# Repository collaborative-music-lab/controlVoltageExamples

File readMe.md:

# controlVoltageExamples

Files for creating Eurorack modules based on the controlVoltage repository: https://github.com/ianhattwick/controlVoltage

### Standard examples
Three examples so far:
* 8-step trigger sequencer
* Sloopy: dual slope generator
* dual LFO (missing?)
* Voxelist: Dual input quantizer

## Also examples of using USB Midi devices to generated sequences

### Requires
Note: all libraries available through library manager
EXCEPT: Control Voltage needs most recent version from Github

1. Arduino USB Host shield 
	* https://github.com/felis/USB_Host_Shield_2.0
2. Hitachi style 2x16 LCD display with I2C backpack
	* https://github.com/marcoschwartz/LiquidCrystal_I2C.git
3. Control Voltage library
	* https://github.com/ianhattwick/controlVoltage
4. Standard EEPROM library

### examples
1. Harpy - Launchkey controlling NiftyCase with melodic voice
2. Leonard - Launchpad 2 controlling NiftyCase with rhythmic voice
3. Tyrone - nanokontrol2 controlling Roland T-8

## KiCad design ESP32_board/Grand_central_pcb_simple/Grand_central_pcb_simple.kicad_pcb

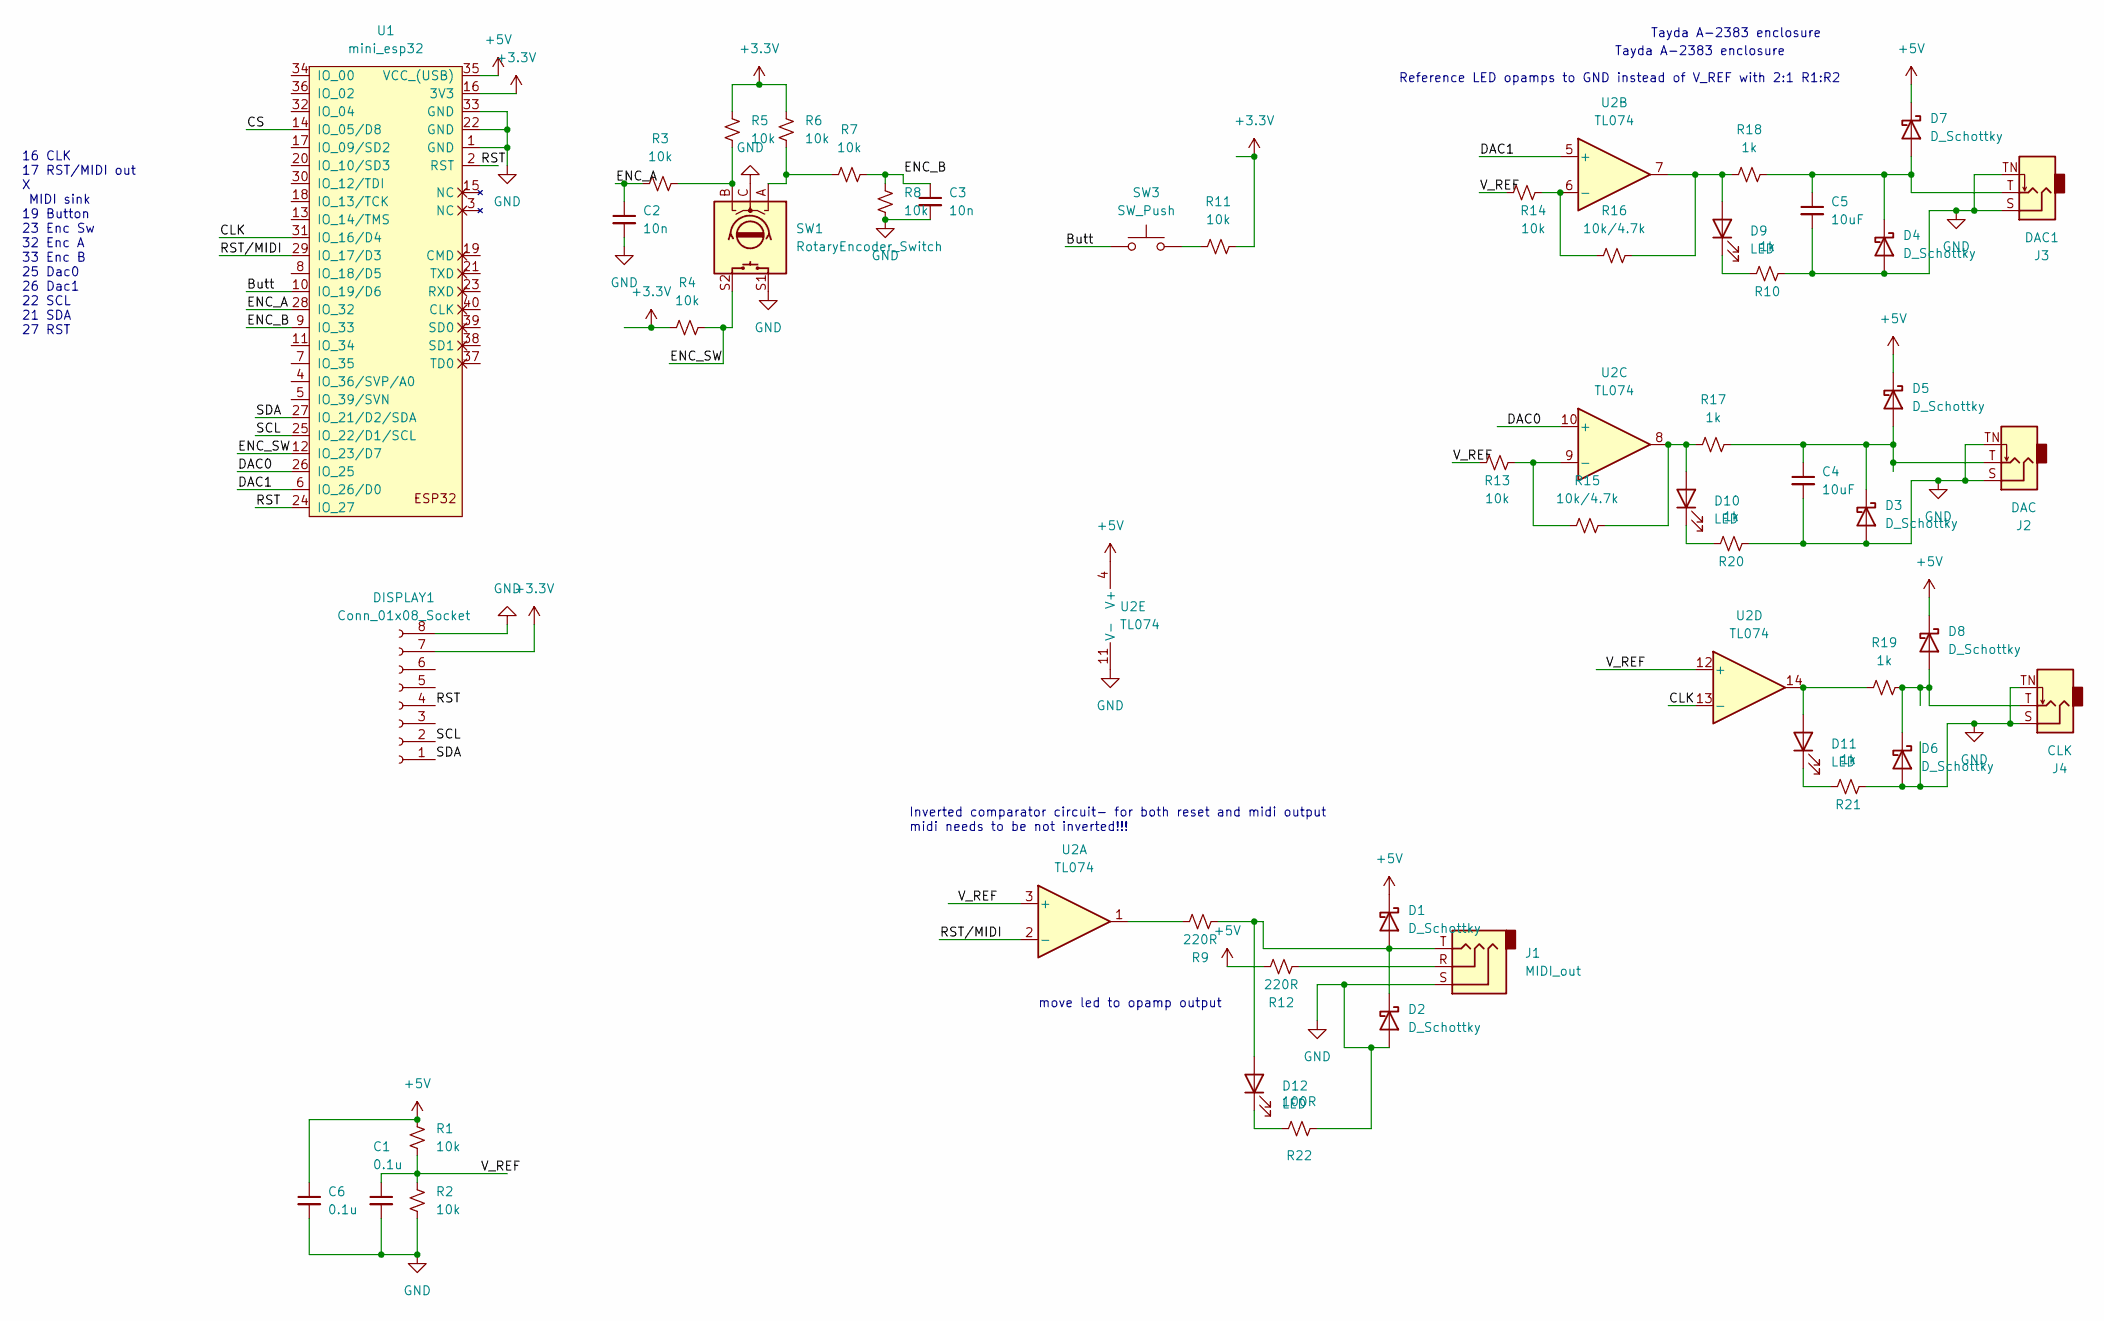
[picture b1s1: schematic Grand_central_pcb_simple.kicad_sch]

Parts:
C1, C6: 0.1u; C_0805_2012Metric_Pad1.18x1.45mm_HandSolder
C2, C3: 10n; C_0805_2012Metric_Pad1.18x1.45mm_HandSolder
C4, C5: 10uF; C_0805_2012Metric_Pad1.18x1.45mm_HandSolder
D1, D2, D3, D4, D5, D6, D7, D8: D_Schottky; D_SOD-123
D9, D10, D11, D12: LED; LED_D3.0mm
DISPLAY1: Conn_01x08_Socket; Adafruit_SSD1306
J1: MIDI_out; Jack_3.5mm_QingPu_WQP-PJ398SM_Vertical_CircularHoles_1
J2: DAC; Jack_3.5mm_QingPu_WQP-PJ398SM_Vertical_CircularHoles
J3: DAC1; Jack_3.5mm_QingPu_WQP-PJ398SM_Vertical_CircularHoles
J4: CLK; Jack_3.5mm_QingPu_WQP-PJ398SM_Vertical_CircularHoles
R1, R2, R3, R4, R5, R6, R7, R8, R11, R13, R14: 10k; R_0805_2012Metric_Pad1.20x1.40mm_HandSolder
R9, R12: 220R; R_0805_2012Metric_Pad1.20x1.40mm_HandSolder
R10, R17, R18, R19, R20, R21: 1k; R_0805_2012Metric_Pad1.20x1.40mm_HandSolder
R15, R16: 10k/4.7k; R_0805_2012Metric_Pad1.20x1.40mm_HandSolder
R22: 100R; R_0805_2012Metric_Pad1.20x1.40mm_HandSolder
SW1: RotaryEncoder_Switch; RotaryEncoder_Alps_EC11E-Switch_Vertical_H20mm_CircularMoun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
SW3: SW_Push; SW_PUSH_6mm_H4.3mm
U1: mini_esp32; ESP32_mini
U2: TL074; SOIC-14_3.9x8.7mm_P1.27mm

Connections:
+3.3V: DISPLAY1.7, R4.1, R5.1, R6.1, R11.2, U1.16 (3V3)
+5V: C6.1, D1.1 (K), D5.1 (K), D7.1 (K), D8.1 (K), R1.1, R12.1, U1.35 (VCC_(USB)), U2.4 (V+)
/Butt: SW3.1, U1.10 (IO_19/D6)
/CLK: U1.31 (IO_16/D4), U2.13 (-)
/CS: U1.14 (IO_05/D8)
/DAC0: U1.26 (IO_25), U2.10 (+)
/DAC1: U1.6 (IO_26/D0), U2.5 (+)
/ENC_A: C2.1, R3.1, U1.28 (IO_32)
/ENC_B: C3.1, R7.2, R8.1, U1.9 (IO_33)
/ENC_SW: R4.2, SW1.S2, U1.12 (IO_23/D7)
/RST: DISPLAY1.4, U1.2 (RST), U1.24 (IO_27)
/RST/MIDI: U1.29 (IO_17/D3), U2.2 (-)
/SCL: DISPLAY1.2, U1.25 (IO_22/D1/SCL)
/SDA: DISPLAY1.1, U1.27 (IO_21/D2/SDA)
/V_REF: C1.1, R1.2, R2.1, R13.2, R14.2, U2.3 (+), U2.12 (+)
GND: C1.2, C2.2, C3.2, C4.2, C5.2, C6.2, D2.2 (A), D3.2 (A), D4.2 (A), D6.2 (A), DISPLAY1.8, J1.S, J2.S, J2.TN, J3.S, J3.TN, J4.S, J4.TN, R2.2, R8.2, R10.1, R20.1, R21.1, R22.1, SW1.C, SW1.S1, U1.1 (GND), U1.22 (GND), U1.33 (GND), U2.11 (V-)
unnamed: D1.2 (A), D2.1 (K), D12.2 (A), J1.T, R9.2
unnamed: C4.1, D3.1 (K), D5.2 (A), J2.T, R17.2
unnamed: C5.1, D4.1 (K), D7.2 (A), J3.T, R18.2
unnamed: D6.1 (K), D8.2 (A), J4.T, R19.2
unnamed: D9.2 (A), R16.2, R18.1, U2.7
unnamed: D9.1 (K), R10.2
unnamed: D10.2 (A), R15.2, R17.1, U2.8
unnamed: D10.1 (K), R20.2
unnamed: D11.2 (A), R19.1, U2.14
unnamed: D11.1 (K), R21.2
unnamed: D12.1 (K), R22.2
unnamed: J1.R, R12.2
unnamed: R3.2, R5.2, SW1.B
unnamed: R6.2, R7.1, SW1.A
unnamed: R9.1, U2.1
unnamed: R11.1, SW3.2
unnamed: R14.1, R16.1, U2.6 (-)
unnamed: R13.1, R15.1, U2.9 (-)

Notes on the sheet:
Reference LED opamps to GND instead of V_REF with 2:1 R1:R2
Tayda A-2383 enclosure
Inverted comparator circuit- for both reset and midi output midi needs to be not inverted!!!
move led to opamp output
16 CLK 17 RST/MIDI out X MIDI sink 19 Button 23 Enc Sw 32 Enc A 33 Enc B 25 Dac0 26 Dac1 22 SCL 21 SDA 27 RST

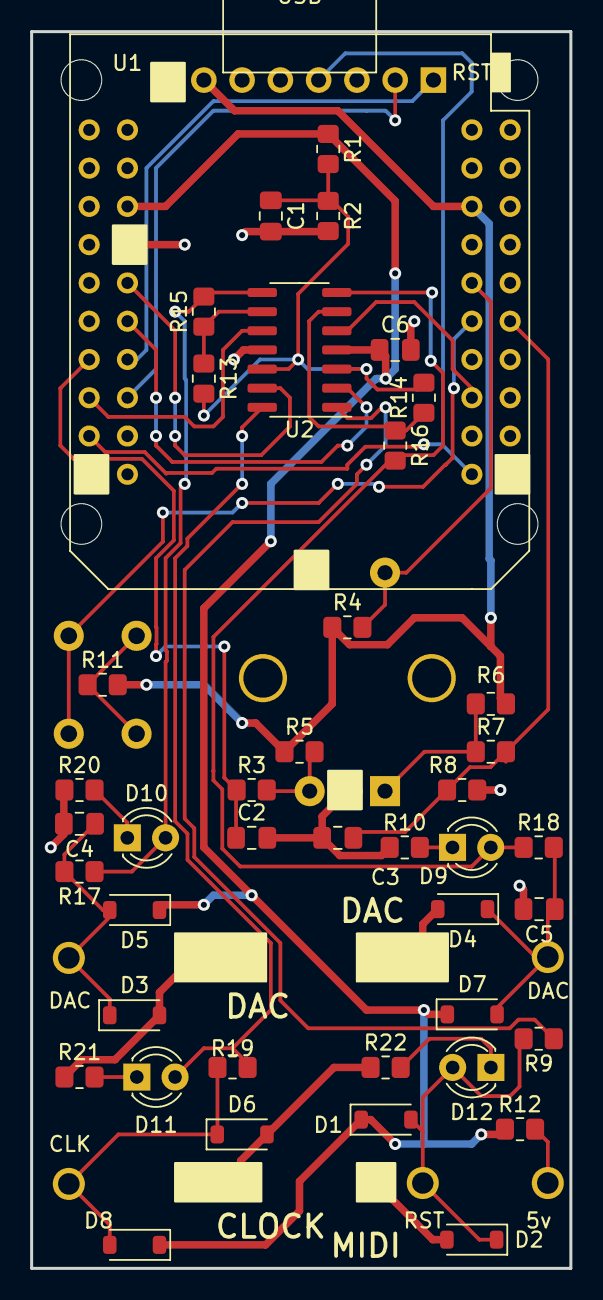
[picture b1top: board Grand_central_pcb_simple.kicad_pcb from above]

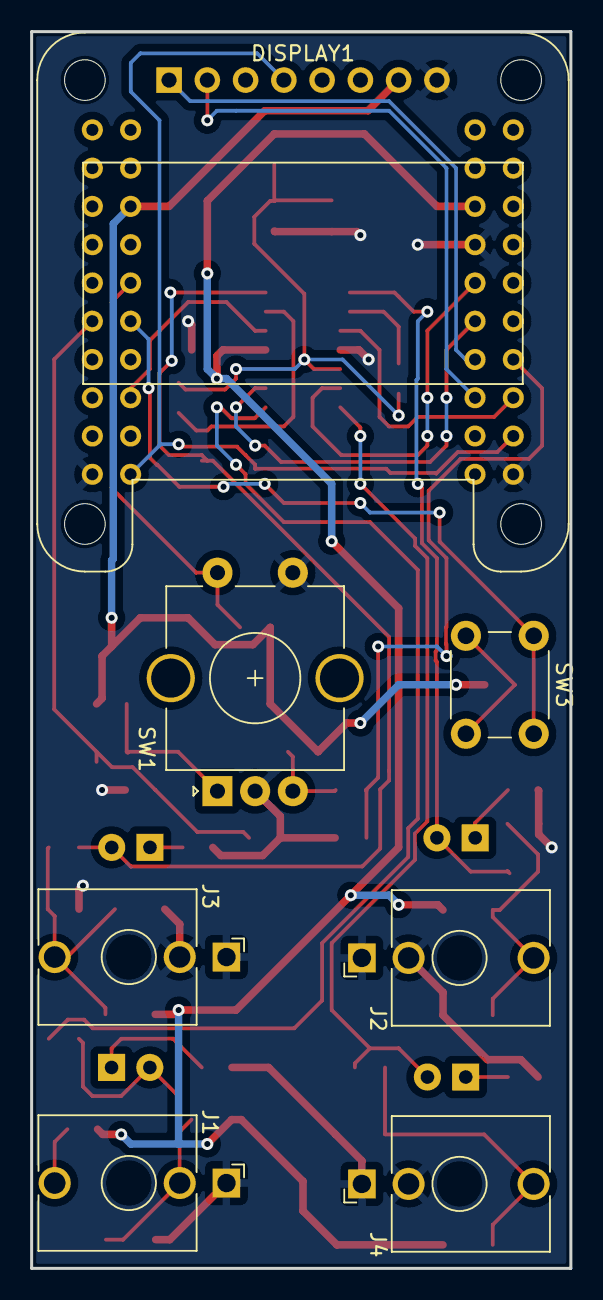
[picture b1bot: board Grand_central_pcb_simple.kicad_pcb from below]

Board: 2 copper layers, 35.8 x 82.1 mm, 49 parts (7 on the bottom side), 33 nets.

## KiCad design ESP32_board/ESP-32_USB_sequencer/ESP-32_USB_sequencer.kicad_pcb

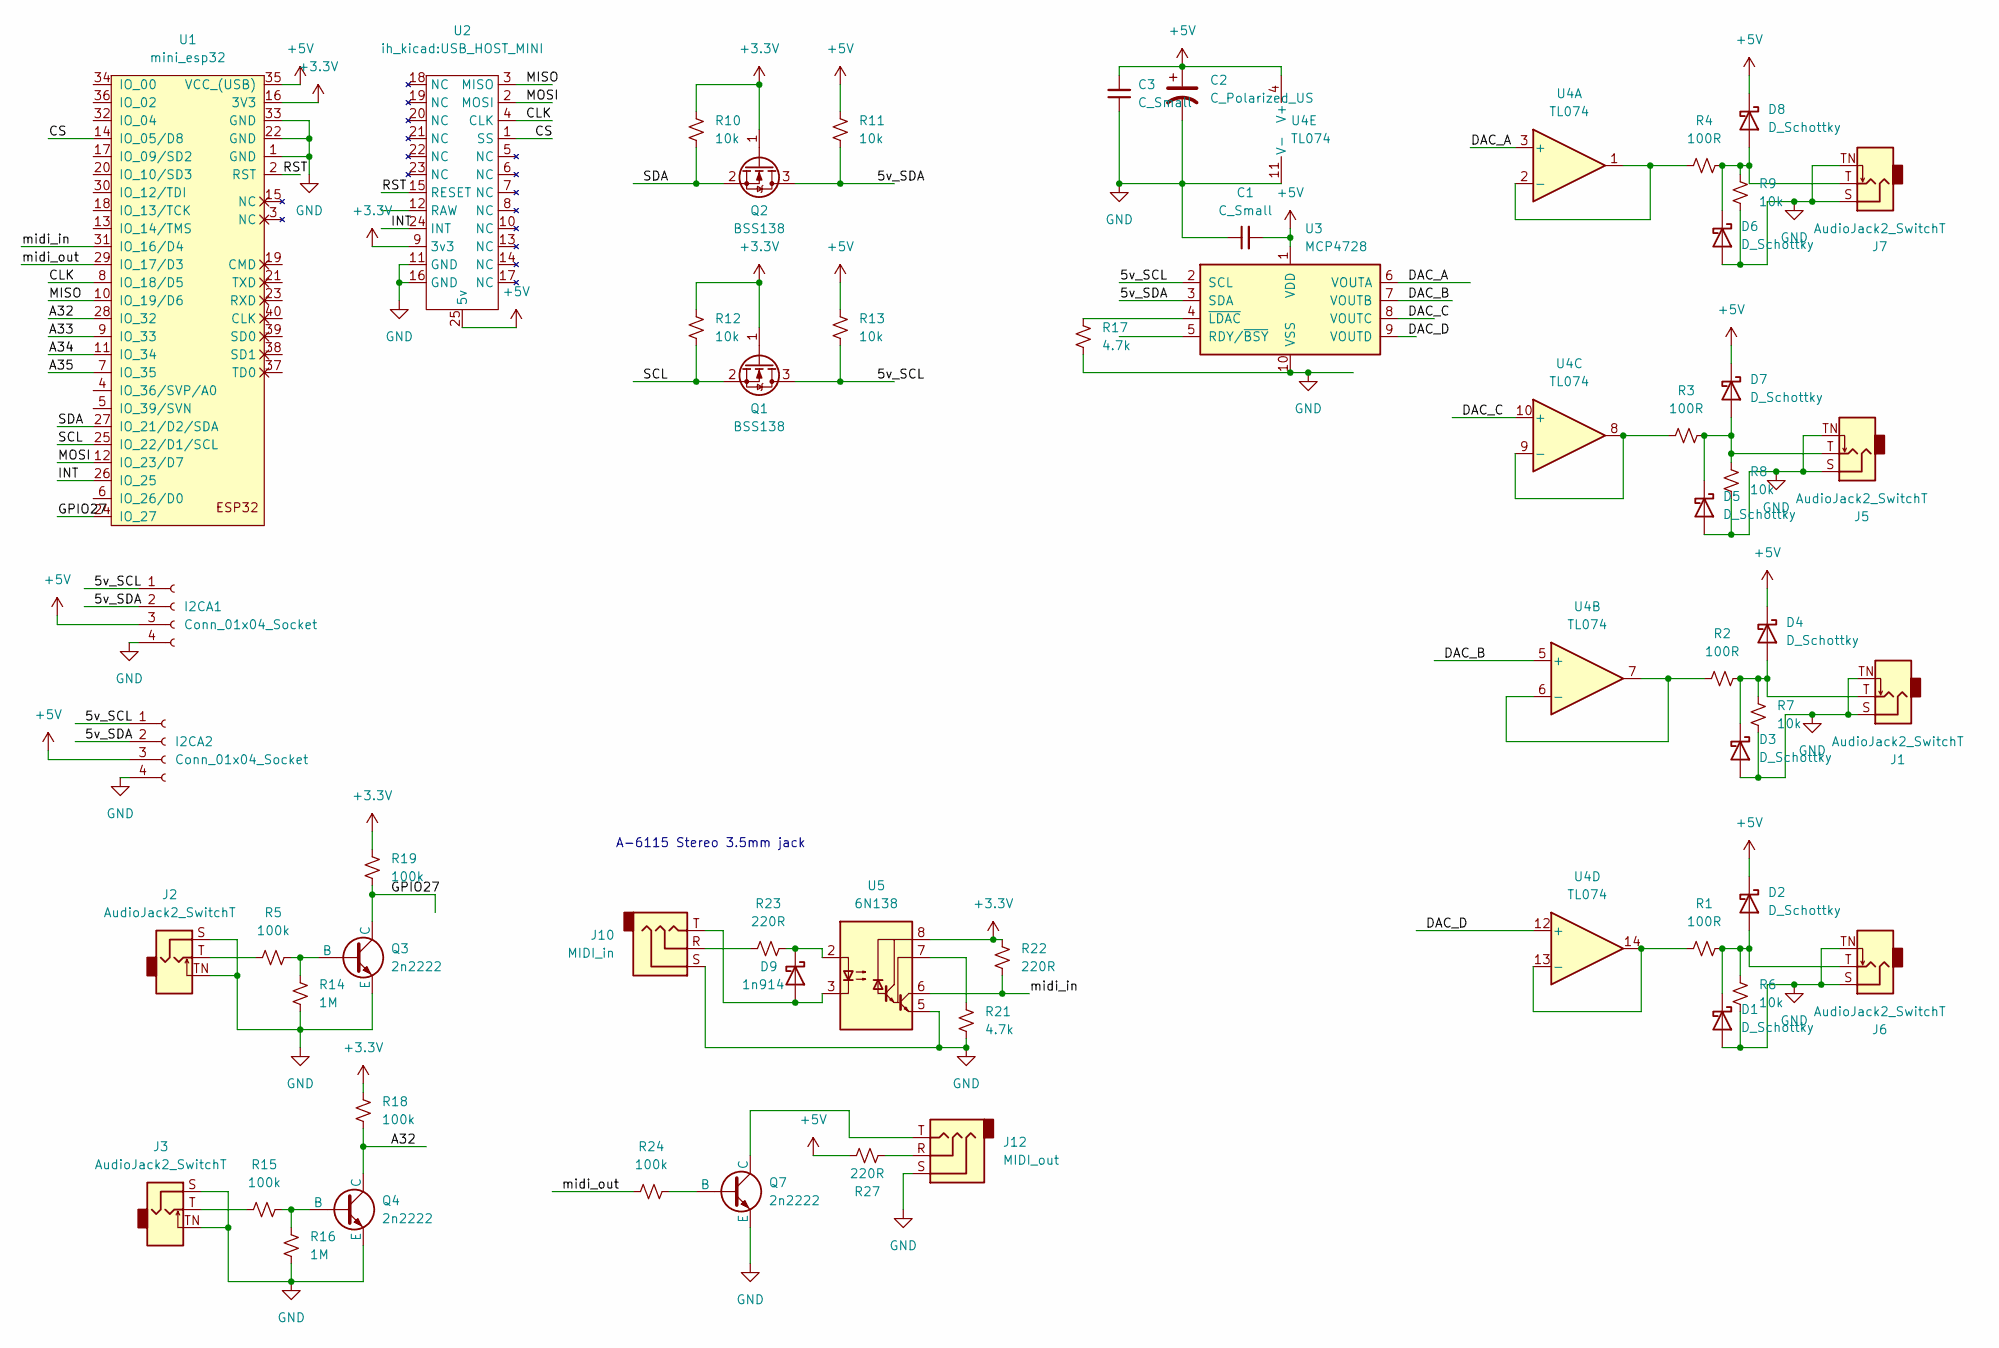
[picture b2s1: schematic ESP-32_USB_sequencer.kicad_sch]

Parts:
C1, C3: C_Small; C_0805_2012Metric_Pad1.18x1.45mm_HandSolder
C2: C_Polarized_US; CP_Radial_D8.0mm_P5.00mm
D1, D2, D3, D4, D5, D6, D7, D8: D_Schottky; D_SOD-123
D9: 1n914; D_5W_P12.70mm_Horizontal
I2CA1, I2CA2: Conn_01x04_Socket; PinHeader_1x04_P2.54mm_Vertical
J1, J2, J3, J5, J6, J7: AudioJack2_SwitchT; Jack_3.5mm_QingPu_WQP-PJ398SM_Vertical_CircularHoles
J10: MIDI_in; Jack_3.5mm_QingPu_WQP-PJ398SM_Vertical_CircularHoles_1
J12: MIDI_out; Jack_3.5mm_QingPu_WQP-PJ398SM_Vertical_CircularHoles_1
Q1, Q2: BSS138; SOT-23
Q3, Q4, Q7: 2n2222; TO-92_Inline_Wide
R1, R2, R3, R4: 100R; R_0805_2012Metric_Pad1.20x1.40mm_HandSolder
R5, R15, R18, R19, R24: 100k; R_Axial_DIN0207_L6.3mm_D2.5mm_P10.16mm_Horizontal
R6, R7, R8, R9: 10k; R_0805_2012Metric_Pad1.20x1.40mm_HandSolder
R10, R11, R12, R13: 10k; R_Axial_DIN0207_L6.3mm_D2.5mm_P10.16mm_Horizontal
R14, R16: 1M; R_Axial_DIN0207_L6.3mm_D2.5mm_P10.16mm_Horizontal
R17: 4.7k; R_0805_2012Metric_Pad1.20x1.40mm_HandSolder
R21: 4.7k; R_Axial_DIN0207_L6.3mm_D2.5mm_P10.16mm_Horizontal
R22, R23, R27: 220R; R_Axial_DIN0207_L6.3mm_D2.5mm_P10.16mm_Horizontal
U1: mini_esp32; ESP32_mini
U2: USB_HOST_MINI
U3: MCP4728; MSOP-10_3x3mm_P0.5mm
U4: TL074; SOIC-14_3.9x8.7mm_P1.27mm
U5: 6N138; DIP-8_W7.62mm

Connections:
+3.3V: Q1.1 (G), Q2.1 (G), R10.2, R12.2, R18.2, R19.2, R22.2, U1.16 (3V3), U2.9 (3v3), U5.8 (VCC)
+5V: C1.2, C2.1, C3.2, D2.1 (K), D4.1 (K), D7.1 (K), D8.1 (K), I2CA1.3, I2CA2.3, R11.2, R13.2, R27.1, U1.35 (VCC_(USB)), U2.25 (5v), U3.1 (VDD), U4.4 (V+)
/5v_SCL: I2CA1.1, I2CA2.1, Q1.3 (D), R13.1, U3.2 (SCL)
/5v_SDA: I2CA1.2, I2CA2.2, Q2.3 (D), R11.1, U3.3 (SDA)
/A32: Q4.1 (C), R18.1, U1.28 (IO_32)
/A33: U1.9 (IO_33)
/A34: U1.11 (IO_34)
/A35: U1.7 (IO_35)
/CLK: U1.8 (IO_18/D5), U2.4 (CLK)
/CS: U1.14 (IO_05/D8), U2.1 (SS)
/DAC_A: U3.6 (VOUTA), U4.3 (+)
/DAC_B: U3.7 (VOUTB), U4.5 (+)
/DAC_C: U3.8 (VOUTC), U4.10 (+)
/DAC_D: U3.9 (VOUTD), U4.12 (+)
/GPIO27: Q3.1 (C), R19.1, U1.24 (IO_27)
/INT: U1.26 (IO_25), U2.24 (INT)
/MISO: U1.10 (IO_19/D6), U2.3 (MISO)
/MOSI: U1.12 (IO_23/D7), U2.2 (MOSI)
/RST: U1.2 (RST), U2.15 (RESET)
/SCL: Q1.2 (S), R12.1, U1.25 (IO_22/D1/SCL)
/SDA: Q2.2 (S), R10.1, U1.27 (IO_21/D2/SDA)
/midi_in: R22.1, U1.31 (IO_16/D4), U5.6 (VO2)
/midi_out: R24.1, U1.29 (IO_17/D3)
GND: C1.1, C2.2, C3.1, D1.2 (A), D3.2 (A), D5.2 (A), D6.2 (A), I2CA1.4, I2CA2.4, J1.S, J1.TN, J2.S, J2.TN, J3.S, J3.TN, J5.S, J5.TN, J6.S, J6.TN, J7.S, J7.TN, J10.S, J12.S, Q3.3 (E), Q4.3 (E), Q7.3 (E), R6.1, R7.1, R8.1, R9.1, R14.1, R16.1, R17.1, R21.1, U1.1 (GND), U1.22 (GND), U1.33 (GND), U2.11 (GND), U2.16 (GND), U3.10 (VSS), U4.11 (V-), U5.5 (GND)
unnamed: D1.1 (K), D2.2 (A), J6.T, R1.2, R6.2
unnamed: D3.1 (K), D4.2 (A), J1.T, R2.2, R7.2
unnamed: D5.1 (K), D7.2 (A), J5.T, R3.2, R8.2
unnamed: D6.1 (K), D8.2 (A), J7.T, R4.2, R9.2
unnamed: D9.2 (A), J10.T, U5.3 (C2)
unnamed: D9.1 (K), R23.1, U5.2 (C1)
unnamed: J2.T, R5.1
unnamed: J3.T, R15.1
unnamed: J10.R, R23.2
unnamed: J12.R, R27.2
unnamed: Q3.2 (B), R5.2, R14.2
unnamed: Q4.2 (B), R15.2, R16.2
unnamed: Q7.2 (B), R24.2
unnamed: J12.T, Q7.1 (C)
unnamed: R17.2, U3.4 (~LDAC)
unnamed: R4.1, U4.1, U4.2 (-)
unnamed: R2.1, U4.6 (-), U4.7
unnamed: R3.1, U4.8, U4.9 (-)
unnamed: R1.1, U4.13 (-), U4.14
unnamed: R21.2, U5.7 (VO1)

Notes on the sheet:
A-6115 Stereo 3.5mm jack

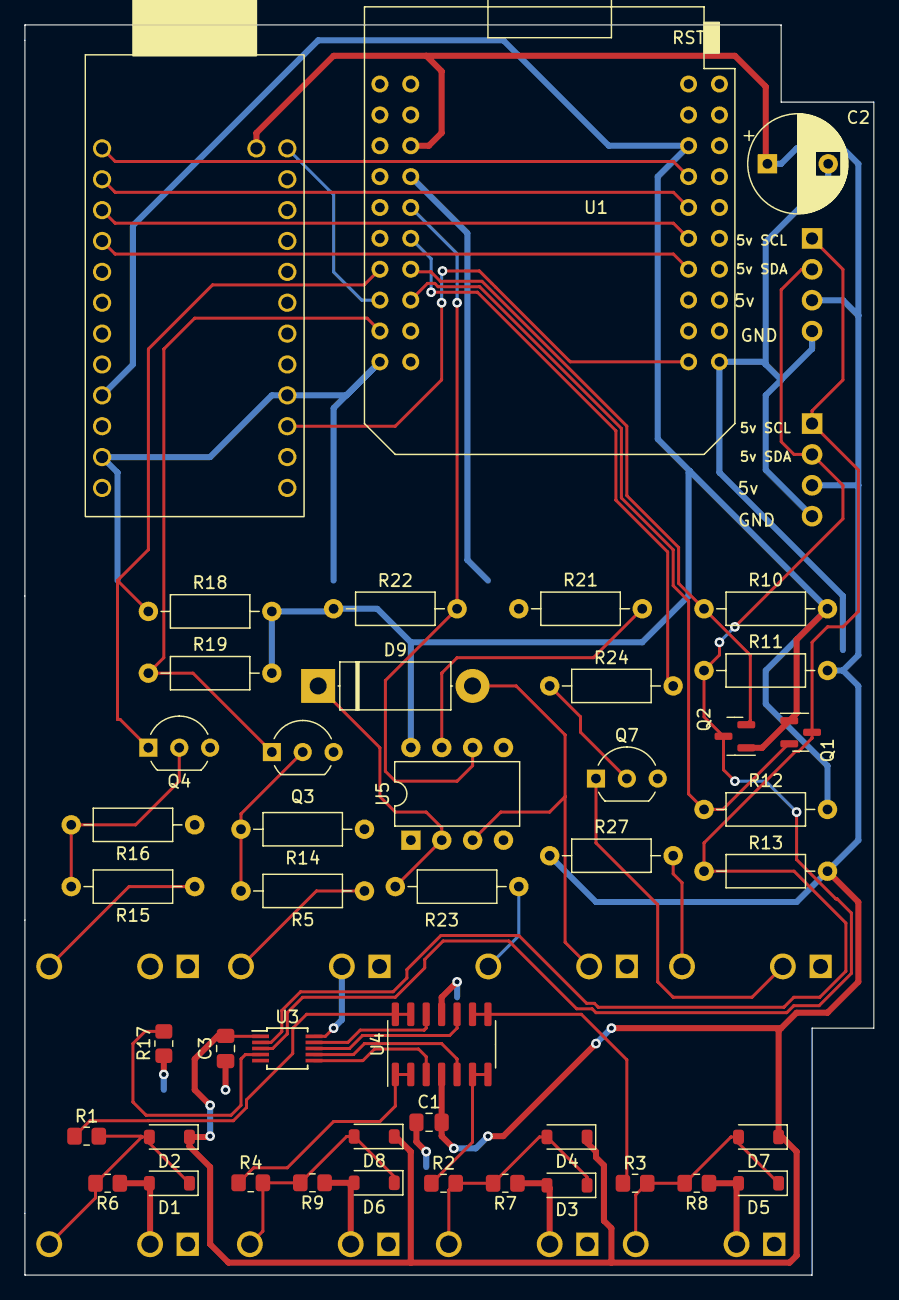
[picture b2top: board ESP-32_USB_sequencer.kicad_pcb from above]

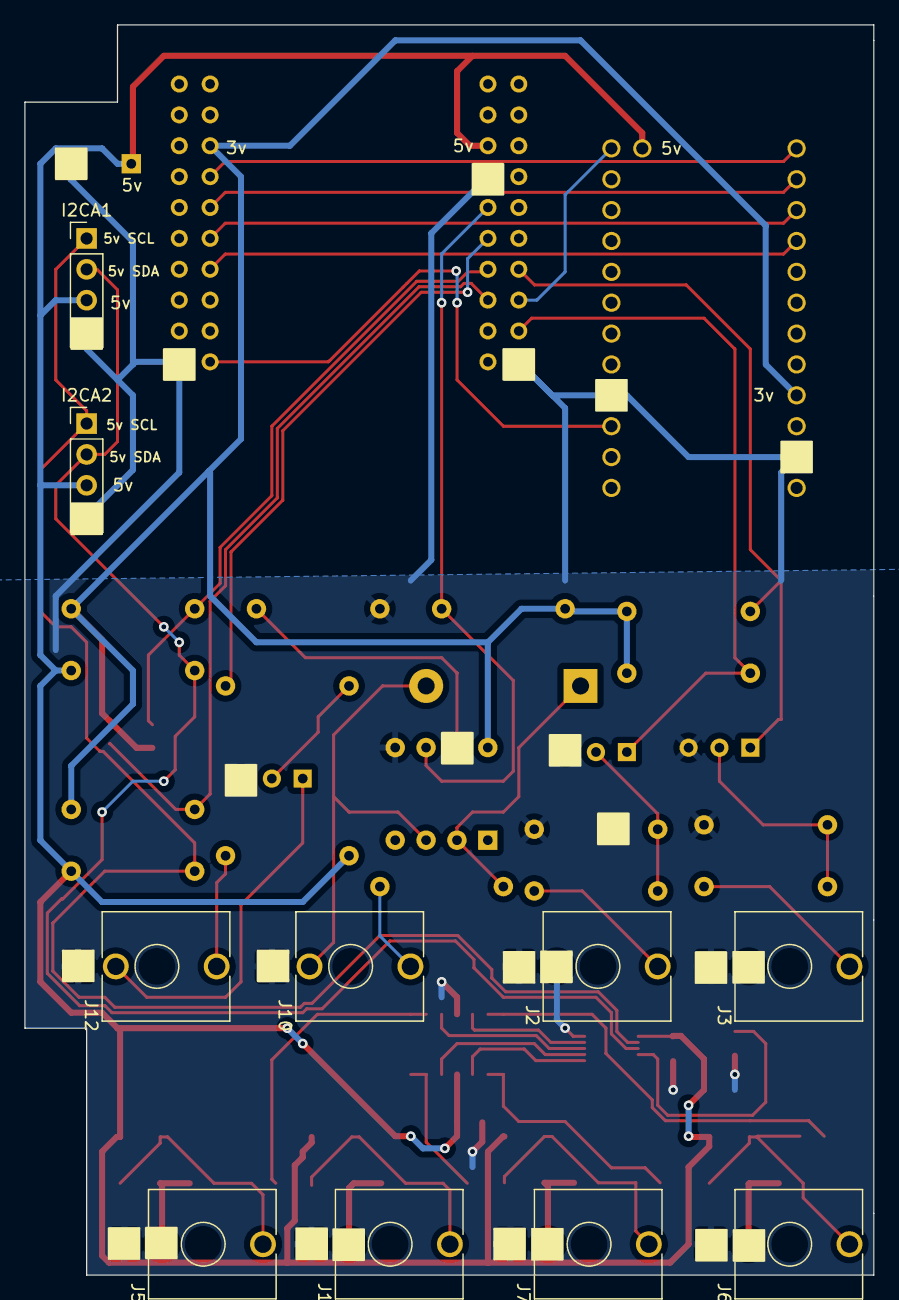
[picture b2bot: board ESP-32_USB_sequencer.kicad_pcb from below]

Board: 2 copper layers, 69.8 x 102.9 mm, 56 parts (10 on the bottom side), 41 nets.

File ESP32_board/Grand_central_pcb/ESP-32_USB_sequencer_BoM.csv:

"Reference","Value","Footprint","Datasheet","Sim.Device","Sim.Pins","Sim.Type","Qty"
"C1, C3","C_Small","Capacitor_SMD:C_0805_2012Metric_Pad1.18x1.45mm_HandSolder","~","","","","2"
"C2","C_Polarized_US","Capacitor_THT:CP_Radial_D8.0mm_P5.00mm","~","","","","1"
"D1-D8","D_Schottky","Diode_SMD:D_SOD-123","~","","","","8"
"D9","1n914","Diode_THT:D_5W_P12.70mm_Horizontal","~","","","","1"
"I2CA1, I2CA2","Conn_01x04_Socket","Connector_PinHeader_2.54mm:PinHeader_1x04_P2.54mm_Vertical","~","","","","2"
"J1-J3, J5-J7","AudioJack2_SwitchT","Connector_Audio:Jack_3.5mm_QingPu_WQP-PJ398SM_Vertical_CircularHoles","~","","","","6"
"J10","MIDI_in","Connector_Audio:Jack_3.5mm_QingPu_WQP-PJ398SM_Vertical_CircularHoles_1","~","","","","1"
"J12","MIDI_out","Connector_Audio:Jack_3.5mm_QingPu_WQP-PJ398SM_Vertical_CircularHoles_1","~","","","","1"
"Q1, Q2","BSS138","Package_TO_SOT_SMD:SOT-23","~","","","","2"
"Q3, Q4, Q7","2n2222","Package_TO_SOT_THT:TO-92_Inline_Wide","~","NPN","1=C 2=B 3=E","GUMMELPOON","3"
"R1-R4","100R","Resistor_SMD:R_0805_2012Metric_Pad1.20x1.40mm_HandSolder","~","","","","4"
"R5, R15, R18, R19, R24","100k","Resistor_THT:R_Axial_DIN0207_L6.3mm_D2.5mm_P10.16mm_Horizontal","~","","","","5"
"R6-R9","10k","Resistor_SMD:R_0805_2012Metric_Pad1.20x1.40mm_HandSolder","~","","","","4"
"R10-R13","10k","Resistor_THT:R_Axial_DIN0207_L6.3mm_D2.5mm_P10.16mm_Horizontal","~","","","","4"
"R14, R16","1M","Resistor_THT:R_Axial_DIN0207_L6.3mm_D2.5mm_P10.16mm_Horizontal","~","","","","2"
"R17","4.7k","Resistor_SMD:R_0805_2012Metric_Pad1.20x1.40mm_HandSolder","~","","","","1"
"R21","4.7k","Resistor_THT:R_Axial_DIN0207_L6.3mm_D2.5mm_P10.16mm_Horizontal","~","","","","1"
"R22, R23, R27","220R","Resistor_THT:R_Axial_DIN0207_L6.3mm_D2.5mm_P10.16mm_Horizontal","~","","","","3"
"U1","mini_esp32","ESP32_mini:ESP32_mini","","","","","1"
"U2","~","ih_kicad:USB_HOST_MINI","","","","","1"
"U3","MCP4728","Package_SO:MSOP-10_3x3mm_P0.5mm","http://ww1.microchip.com/downloads/en/DeviceDoc/22187E.pdf","","","","1"
"U4","TL074","Package_SO:SOIC-14_3.9x8.7mm_P1.27mm","http://www.ti.com/lit/ds/symlink/tl071.pdf","","","","1"
"U5","6N138","Package_DIP:DIP-8_W7.62mm","http://www.onsemi.com/pub/Collateral/HCPL2731-D.pdf","","","","1"

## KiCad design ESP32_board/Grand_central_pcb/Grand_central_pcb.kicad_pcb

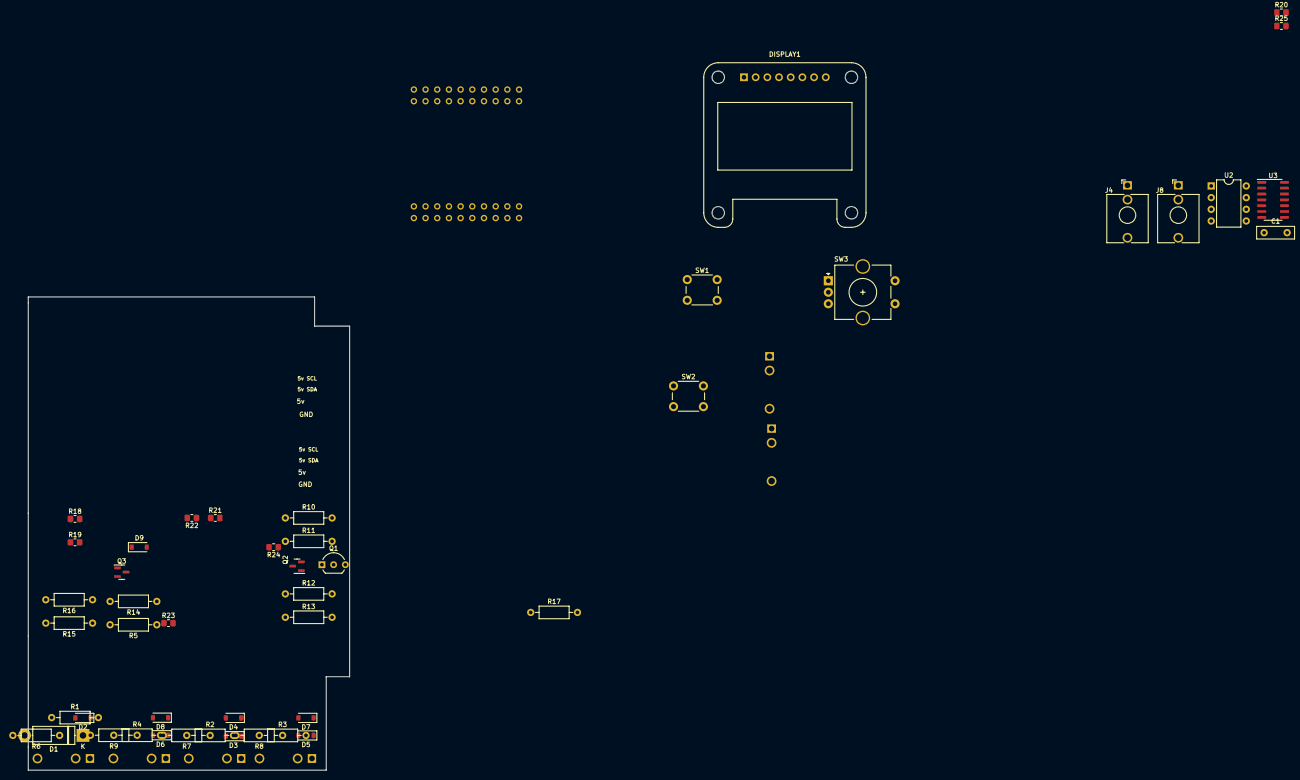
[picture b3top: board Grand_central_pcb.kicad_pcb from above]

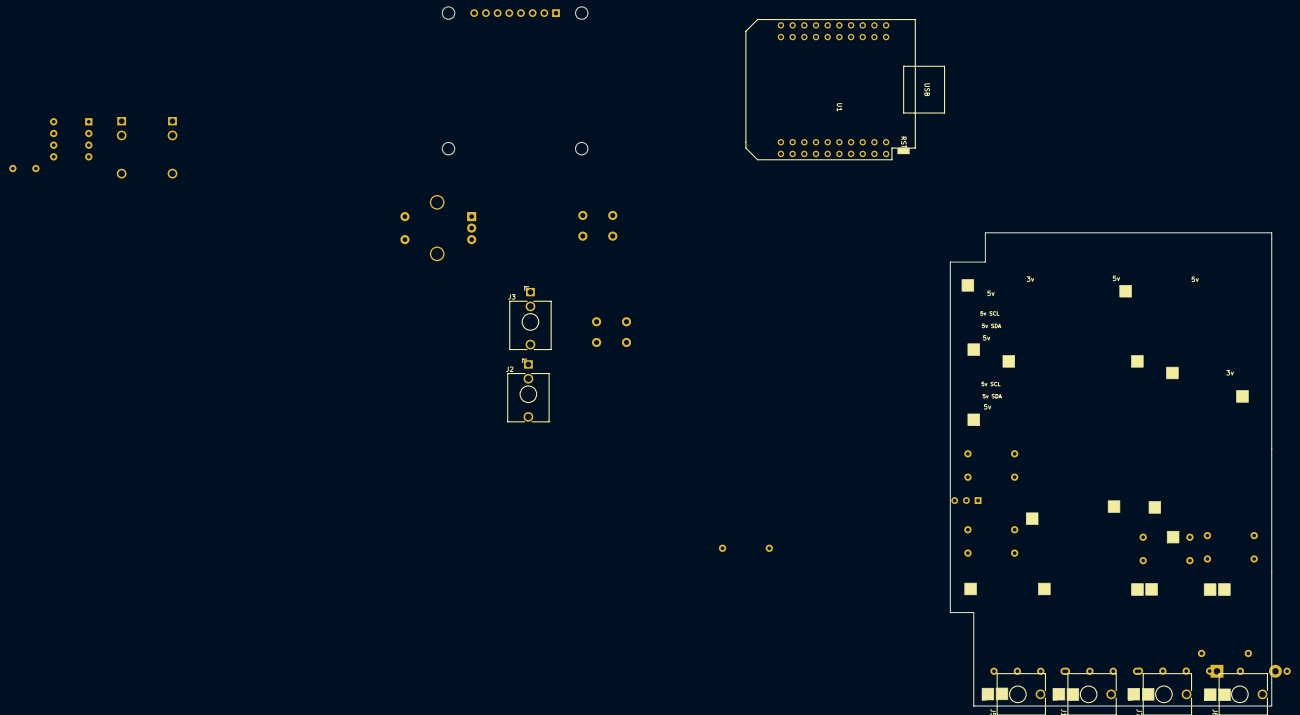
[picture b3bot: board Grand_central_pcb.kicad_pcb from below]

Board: 2 copper layers, 69.8 x 102.9 mm, 53 parts (7 on the bottom side), 36 nets, no tracks yet.

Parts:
C1: C_Small; C_Disc_D8.0mm_W2.5mm_P5.00mm
D1: 1n914; D_5W_P12.70mm_Horizontal
D2, D3, D4, D5, D6, D7, D8, D9: D_Schottky; D_SOD-123
DISPLAY1: Conn_01x08_Socket; Adafruit_SSD1306
J1, J2, J5, J6, J7, J8: AudioJack2_SwitchT; Jack_3.5mm_QingPu_WQP-PJ398SM_Vertical_CircularHoles
J3: MIDI_in; Jack_3.5mm_QingPu_WQP-PJ398SM_Vertical_CircularHoles_1
J4: MIDI_out; Jack_3.5mm_QingPu_WQP-PJ398SM_Vertical_CircularHoles_1
Q1: 2n2222; TO-92_Inline_Wide
Q2, Q3: BSS138; SOT-23
R1, R2, R5, R6: 100k; R_Axial_DIN0207_L6.3mm_D2.5mm_P10.16mm_Horizontal
R3, R4: 1M; R_Axial_DIN0207_L6.3mm_D2.5mm_P10.16mm_Horizontal
R7, R8, R11, R12, R16, R17: 10k; R_Axial_DIN0207_L6.3mm_D2.5mm_P10.16mm_Horizontal
R9, R10, R13, R15: 220R; R_Axial_DIN0207_L6.3mm_D2.5mm_P10.16mm_Horizontal
R14: 4.7k; R_Axial_DIN0207_L6.3mm_D2.5mm_P10.16mm_Horizontal
R18, R19, R20, R21, R22, R23, R24, R25: 100R; R_0805_2012Metric_Pad1.20x1.40mm_HandSolder
SW1, SW2: SW_Push; SW_PUSH_6mm_H4.3mm
SW3: RotaryEncoder_Switch; RotaryEncoder_Alps_EC11E-Switch_Vertical_H20mm_CircularMoun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
U1: mini_esp32; ESP32_mini
U2: 6N138; DIP-8_W7.62mm
U3: TL074; SOIC-14_3.9x8.7mm_P1.27mm

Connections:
+3.3V: DISPLAY1.8, Q2.1 (G), Q3.1 (G), R5.2, R7.2, R8.2, R15.2, U1.16 (3V3), U2.8 (VCC)
+5V: D5.1 (K), D7.1 (K), D8.1 (K), D9.1 (K), R11.2, R12.2, R13.1, R16.1, U1.35 (VCC_(USB))
/5v_SCL: Q3.3 (D), R12.1
/5v_SDA: Q2.3 (D), R11.1
/DAC0: U1.26 (IO_25), U3.3 (+)
/DAC1: U1.6 (IO_26/D0), U3.10 (+)
/GPIO27: R5.1, U1.24 (IO_27)
/RST: DISPLAY1.4, U1.2 (RST)
/SCL: DISPLAY1.2, Q3.2 (S), R8.1, U1.25 (IO_22/D1/SCL)
/SDA: DISPLAY1.1, Q2.2 (S), R7.1, U1.27 (IO_21/D2/SDA)
/V_REF: R18.2, R19.2, U3.13 (-), U3.14
/midi_in: R15.1, U1.31 (IO_16/D4), U2.6 (VO2)
/midi_out: R6.1, U1.29 (IO_17/D3)
GND: C1.2, D2.2 (A), D3.2 (A), D4.2 (A), D6.2 (A), DISPLAY1.7, J1.S, J1.TN, J2.S, J2.TN, J3.S, J4.S, J5.S, J5.TN, J6.S, J6.TN, J7.S, J7.TN, J8.S, J8.TN, Q1.3 (E), R3.1, R4.1, R14.1, R17.2, U1.1 (GND), U1.22 (GND), U1.33 (GND), U2.5 (GND)
unnamed: D1.2 (A), J3.T, U2.3 (C2)
unnamed: D1.1 (K), R9.1, U2.2 (C1)
unnamed: D2.1 (K), D5.2 (A), J5.T, R22.2
unnamed: D3.1 (K), D7.2 (A), J6.T, R23.2
unnamed: D4.1 (K), D8.2 (A), J7.T, R24.2
unnamed: D6.1 (K), D9.2 (A), J8.T, R25.2
unnamed: J1.T, R1.1
unnamed: J2.T, R2.1
unnamed: J3.R, R9.2
unnamed: J4.R, R13.2
unnamed: J4.T, R10.2
unnamed: Q1.2 (B), R6.2
unnamed: Q1.1 (C), R10.1
unnamed: R1.2, R3.2
unnamed: R2.2, R4.2
unnamed: R20.2, R22.1, U3.8
unnamed: R21.2, R23.1, U3.1
unnamed: R14.2, U2.7 (VO1)
unnamed: R19.1, R21.1, U3.2 (-)
unnamed: R25.1, U3.6 (-), U3.7
unnamed: R18.1, R20.1, U3.9 (-)
unnamed: C1.1, R16.2, R17.1, U3.12 (+)

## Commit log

2022-03-20 Add copernicus
2022-04-01 Added sloop
2022-05-05 Update copernicus
2022-05-05 add passive folder
2022-05-05 Passive Modules Initial Commit
2022-05-05 Fix markdown issue for Multipliers
2023-01-30 update voxeist
2023-01-30 copernicus still in dev
2023-01-30 not sure
2023-01-30 Create tyrone
2023-01-31 updating todo list
2023-02-01 Create Harpy
2023-02-05 working on timing issues
2023-02-05 controller/synth defs
2023-02-05 created leonard
2023-02-05 created leopard
    obsoleted by leonard
2023-02-05 Rename readMe.txt to readMe.md
2023-02-06 Working on clock multiplication timing
2023-02-06 Updating Clock timing
    Also added scheduleNoteOff functions
2023-02-10 updated clock
2023-02-23 catching up to date
2023-03-17 create bob v1
2023-03-17 create leonard v2
2023-03-17 archive for leonard v2_0
2023-03-17 update leonard v2
2023-03-17 tyrone bug fixes
2023-03-17 Lyra updates
2023-11-09 added test midi clock
2023-11-09 added support for esp32
2024-04-28 lots of stuff
2024-07-02 grand central pcb gerbers
2025-06-22 grand
